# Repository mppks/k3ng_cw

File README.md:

# K3NG CW keyer yet another version...

## Schematic K3NG CW keyer

## Applying my settings
To use my keyer settings, copy the files from the _r1tbj_settings_ directory to the original [k3ng firmware](https://github.com/k3ng/k3ng_cw_keyer) directory and add the following line to the **keyer_hardware.h** file

```C
#define HARDWARE_R1TBJ
```

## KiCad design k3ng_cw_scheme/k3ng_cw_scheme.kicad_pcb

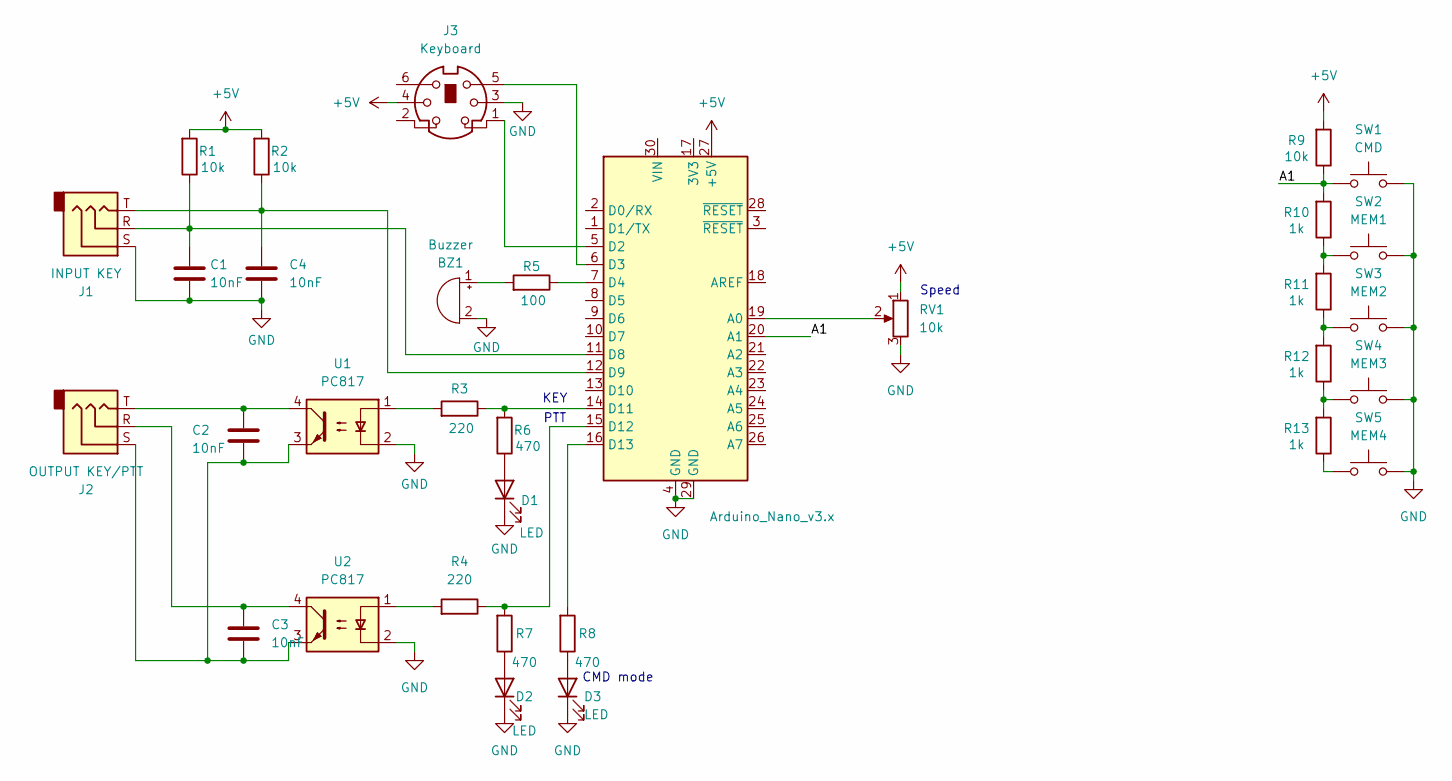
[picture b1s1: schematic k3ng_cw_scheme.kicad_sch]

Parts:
A1: Arduino_Nano_v3.x; Arduino_Nano
BZ1: Buzzer; Buzzer_12x9.5RM7.6
C1, C2, C3, C4: 10nF; C_Disc_D5.0mm_W2.5mm_P2.50mm
D1, D2, D3: LED; LED_D3.0mm
J1: INPUT KEY; Jack_3.5mm_CUI_SJ1-3525N_Horizontal
J2: OUTPUT KEY/PTT; Jack_3.5mm_CUI_SJ1-3525N_Horizontal
J3: Keyboard; Connector_Mini-DIN_Female_6Pin_2rows
R1, R2: 10k; R_Axial_DIN0204_L3.6mm_D1.6mm_P5.08mm_Vertical
R3, R4: 220; R_Axial_DIN0204_L3.6mm_D1.6mm_P5.08mm_Vertical
R5: 100; R_Axial_DIN0204_L3.6mm_D1.6mm_P5.08mm_Vertical
R6, R7, R8: 470; R_Axial_DIN0204_L3.6mm_D1.6mm_P5.08mm_Vertical
R9: 10k; R_Axial_DIN0207_L6.3mm_D2.5mm_P10.16mm_Horizontal
R10, R11, R12, R13: 1k; R_Axial_DIN0207_L6.3mm_D2.5mm_P10.16mm_Horizontal
RV1: 10k; Potentiometer_Alpha_RD901F-40-00D_Single_Vertical
SW1: CMD; SW_SPST_Omron_B3F-50xx
SW2: MEM1; SW_SPST_Omron_B3F-50xx
SW3: MEM2; SW_SPST_Omron_B3F-50xx
SW4: MEM3; SW_SPST_Omron_B3F-50xx
SW5: MEM4; SW_SPST_Omron_B3F-50xx
U1, U2: PC817; DIP-4_W7.62mm

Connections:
+5V: A1.27 (+5V), J3.4, R1.2, R2.2, R9.2, RV1.1
/A1: A1.20 (A1), R9.1, R10.2, SW1.1
GND: A1.4 (GND), A1.29 (GND), BZ1.2 (-), C1.2, C4.2, D1.1 (K), D2.1 (K), D3.1 (K), J1.S, J3.3, RV1.3, SW1.2, SW2.2, SW3.2, SW4.2, SW5.2, U1.2, U2.2
unnamed: A1.19 (A0), RV1.2
unnamed: A1.5 (D2), J3.1
unnamed: A1.6 (D3), J3.5
unnamed: A1.7 (D4), R5.1
unnamed: A1.11 (D8), C1.1, J1.R, R1.1
unnamed: A1.12 (D9), C4.1, J1.T, R2.1
unnamed: A1.14 (D11), R3.1, R6.2
unnamed: A1.15 (D12), R4.1, R7.2
unnamed: A1.16 (D13), R8.2
unnamed: BZ1.1 (+), R5.2
unnamed: C2.1, J2.T, U1.4
unnamed: C2.2, C3.2, J2.S, U1.3, U2.3
unnamed: C3.1, J2.R, U2.4
unnamed: D1.2 (A), R6.1
unnamed: D2.2 (A), R7.1
unnamed: D3.2 (A), R8.1
unnamed: R3.2, U1.1
unnamed: R4.2, U2.1
unnamed: R10.1, R11.2, SW2.1
unnamed: R11.1, R12.2, SW3.1
unnamed: R12.1, R13.2, SW4.1
unnamed: R13.1, SW5.1

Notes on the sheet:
KEY
CMD mode
PTT
Speed

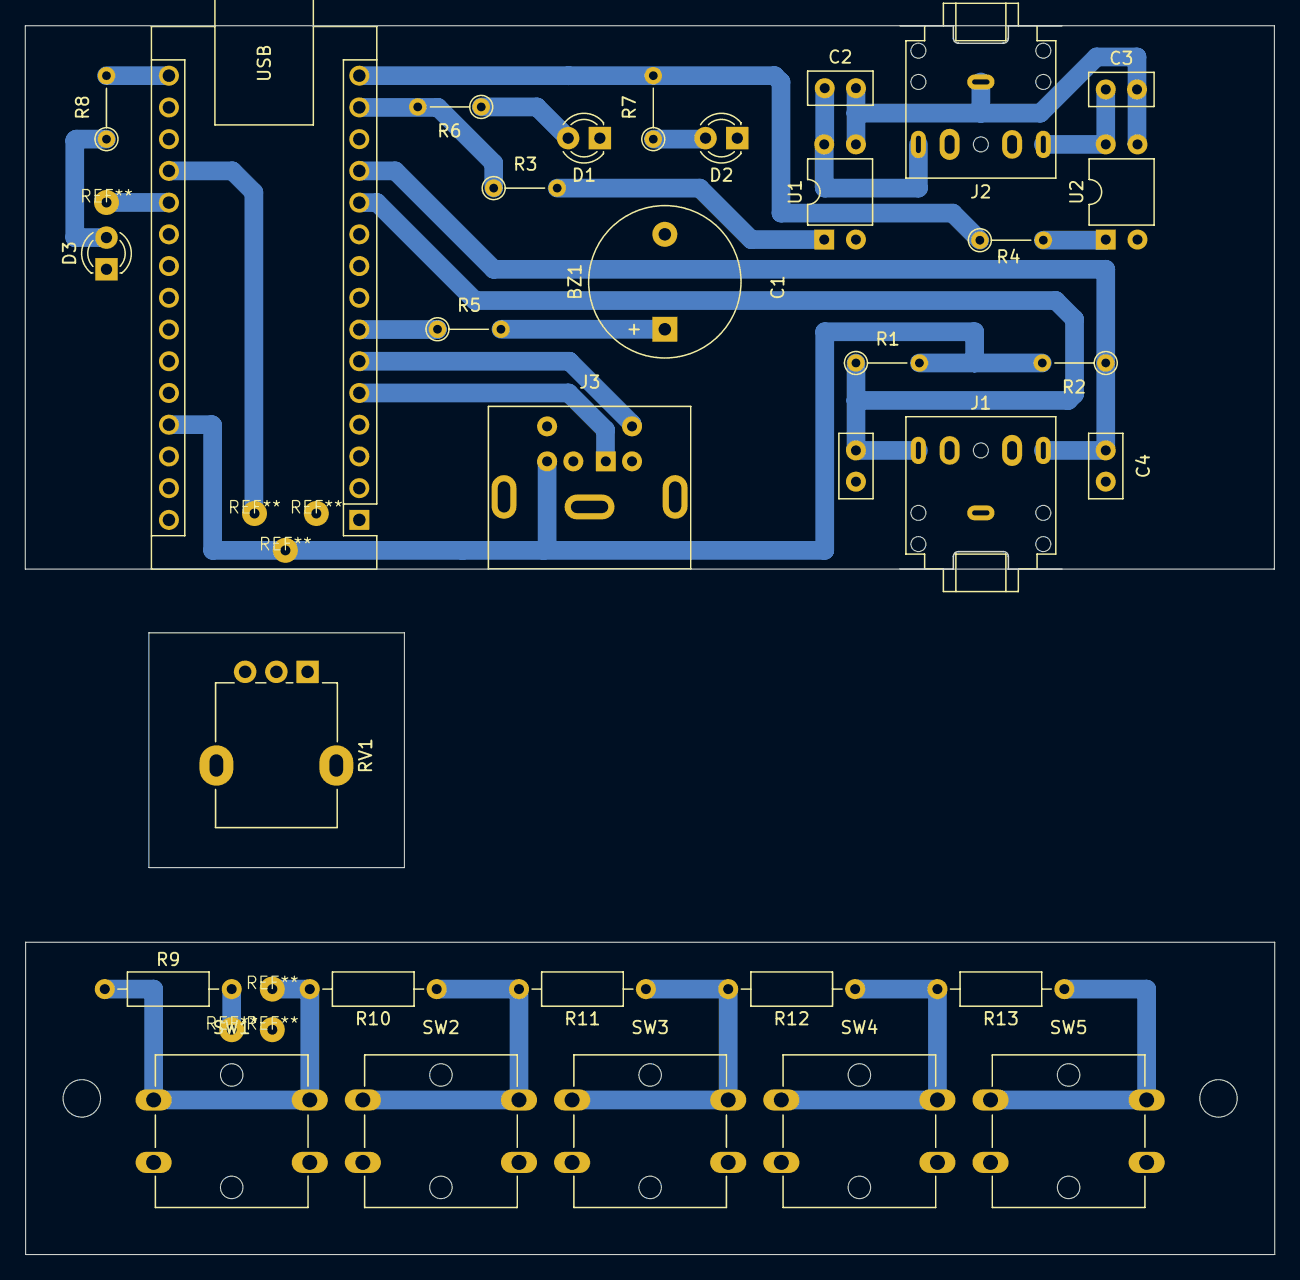
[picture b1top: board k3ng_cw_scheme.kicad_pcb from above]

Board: 2 copper layers, 100.0 x 98.3 mm, 33 parts (0 on the bottom side), 25 nets.

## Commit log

2025-05-19 Add keyboard connector Start working on PCB
2025-06-03 Add some pads to pcb
2025-06-04 Add firmware configuration files
2025-06-05 Add scheme to pdf
2026-02-23 chore(k3ng_cw_keyer): add the firmware repository as a module
2026-02-24 docs(README.md): add an electronic circuit to the description
